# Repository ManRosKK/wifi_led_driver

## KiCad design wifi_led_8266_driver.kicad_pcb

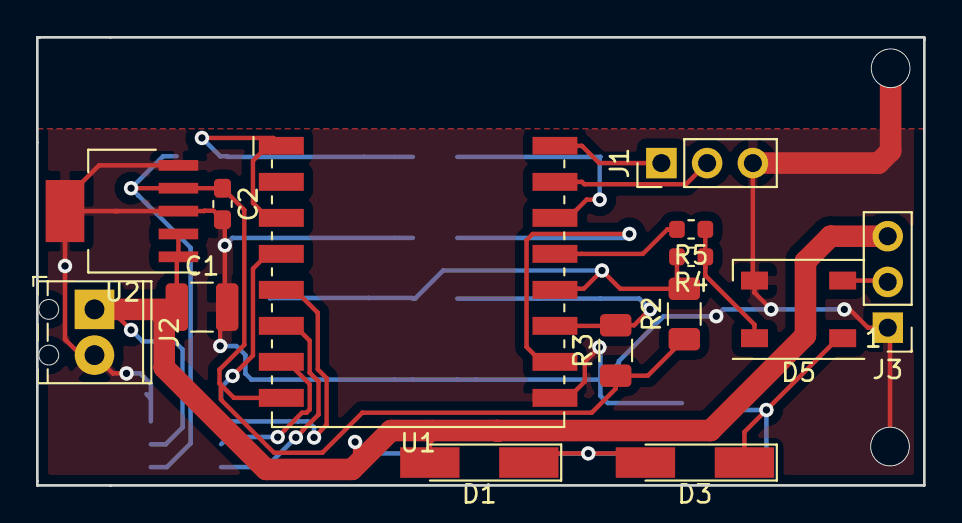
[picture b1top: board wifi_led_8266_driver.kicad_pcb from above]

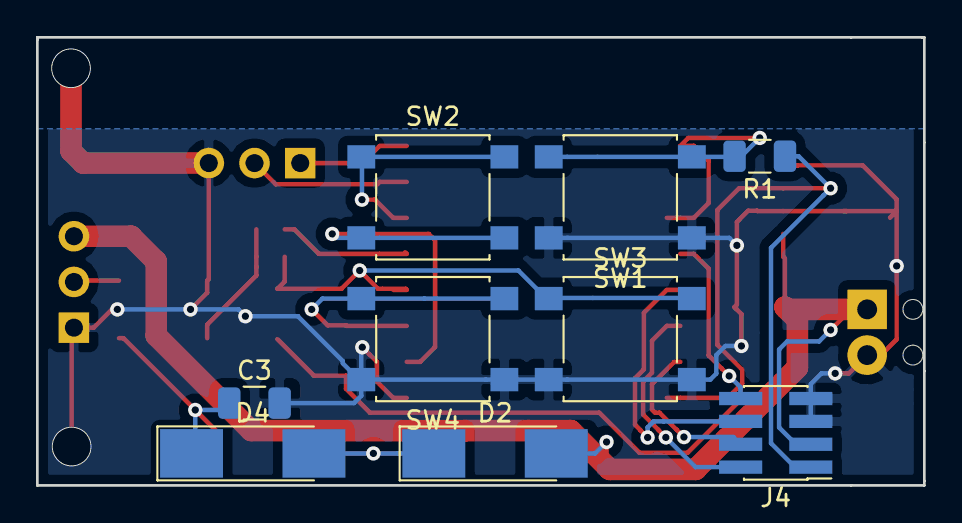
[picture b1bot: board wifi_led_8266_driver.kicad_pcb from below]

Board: 2 copper layers, 49.3 x 24.9 mm, 23 parts (9 on the bottom side), 19 nets.

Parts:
C1: 4.7uF; C_1210_3225Metric
C2: 1uF; C_0603_1608Metric_Pad1.05x0.95mm_HandSolder
C3: 100nf; C_1206_3216Metric
D1, D3: D; D_MiniMELF_Handsoldering
D2, D4: D; D_MELF_Handsoldering
D5: WS2812B; LED_WS2812B_PLCC4_5.0x5.0mm_P3.2mm
J1: UART; PinHeader_1x03_P2.54mm_Vertical
J2: POWER; TerminalBlock_Phoenix_MPT-0,5-2-2.54_1x02_P2.54mm_Horizontal
J3: WS2812B_DRIVER; PinHeader_1x03_P2.54mm_Vertical
J4: Conn_02x04_Odd_Even; PinHeader_2x04_P1.27mm_Vertical_SMD
R1, R2, R3: 10K; R_1206_3216Metric
R4: SB1; R_0603_1608Metric
R5: SB2; R_0603_1608Metric
SW1: RESET_BTN; SW_SPST_B3S-1000
SW2: BUTTON; SW_SPST_B3S-1000
SW3: FLASH_BTN; SW_SPST_B3S-1000
SW4: BOOT_BTN; SW_SPST_B3S-1000
U1: ESP-07
U2: MCP1825T; SOT-223-6

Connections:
+3V3: C2.1, J4.1, R1.1, R2.1, R3.1, U1.8, U2.4
/5V_INP: C1.1, D1.2, D2.2, J2.1, J3.3, J4.3, U2.1, U2.2
/GPIO0: R2.2, R4.2, SW3.1, U1.12
/GPIO2: R3.2, SW4.2, U1.11
/GPIO12: J4.2, U1.6
/GPIO13: J4.4, U1.7
/GPIO14: J4.6, U1.5
/GPIO16: J4.8, U1.4
/RX: J1.2, U1.15
/TX: J1.1, U1.16
/WS2812B_DATA: D5.2, J3.2
GND: C1.2, C2.2, C3.2, D5.3, J1.3, J2.2, J3.1, J4.5, J4.7, SW1.1, SW3.2, SW4.1, U1.9, U2.3, U2.5, U2.6
unnamed: C3.1, D3.1, D4.1, D5.1
unnamed: D1.1, D2.1, D3.2, D4.2
unnamed: D5.4, R4.1, R5.1
unnamed: R1.2, SW1.2, U1.1, U1.3
unnamed: R5.2, U1.13
unnamed: SW2.1, U1.14
unnamed: SW2.2, U1.10

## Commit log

2018-09-12 init commit
2018-09-16 layout for enclouser https://www.tme.eu/pl/details/hm-1551usb3tsk/obudowy-uniwersalne/hammond/1551usb3tsk/
2018-09-17 propozycja
2018-09-17 propozycja skonczona
2018-09-25 wersja produkcyjna
